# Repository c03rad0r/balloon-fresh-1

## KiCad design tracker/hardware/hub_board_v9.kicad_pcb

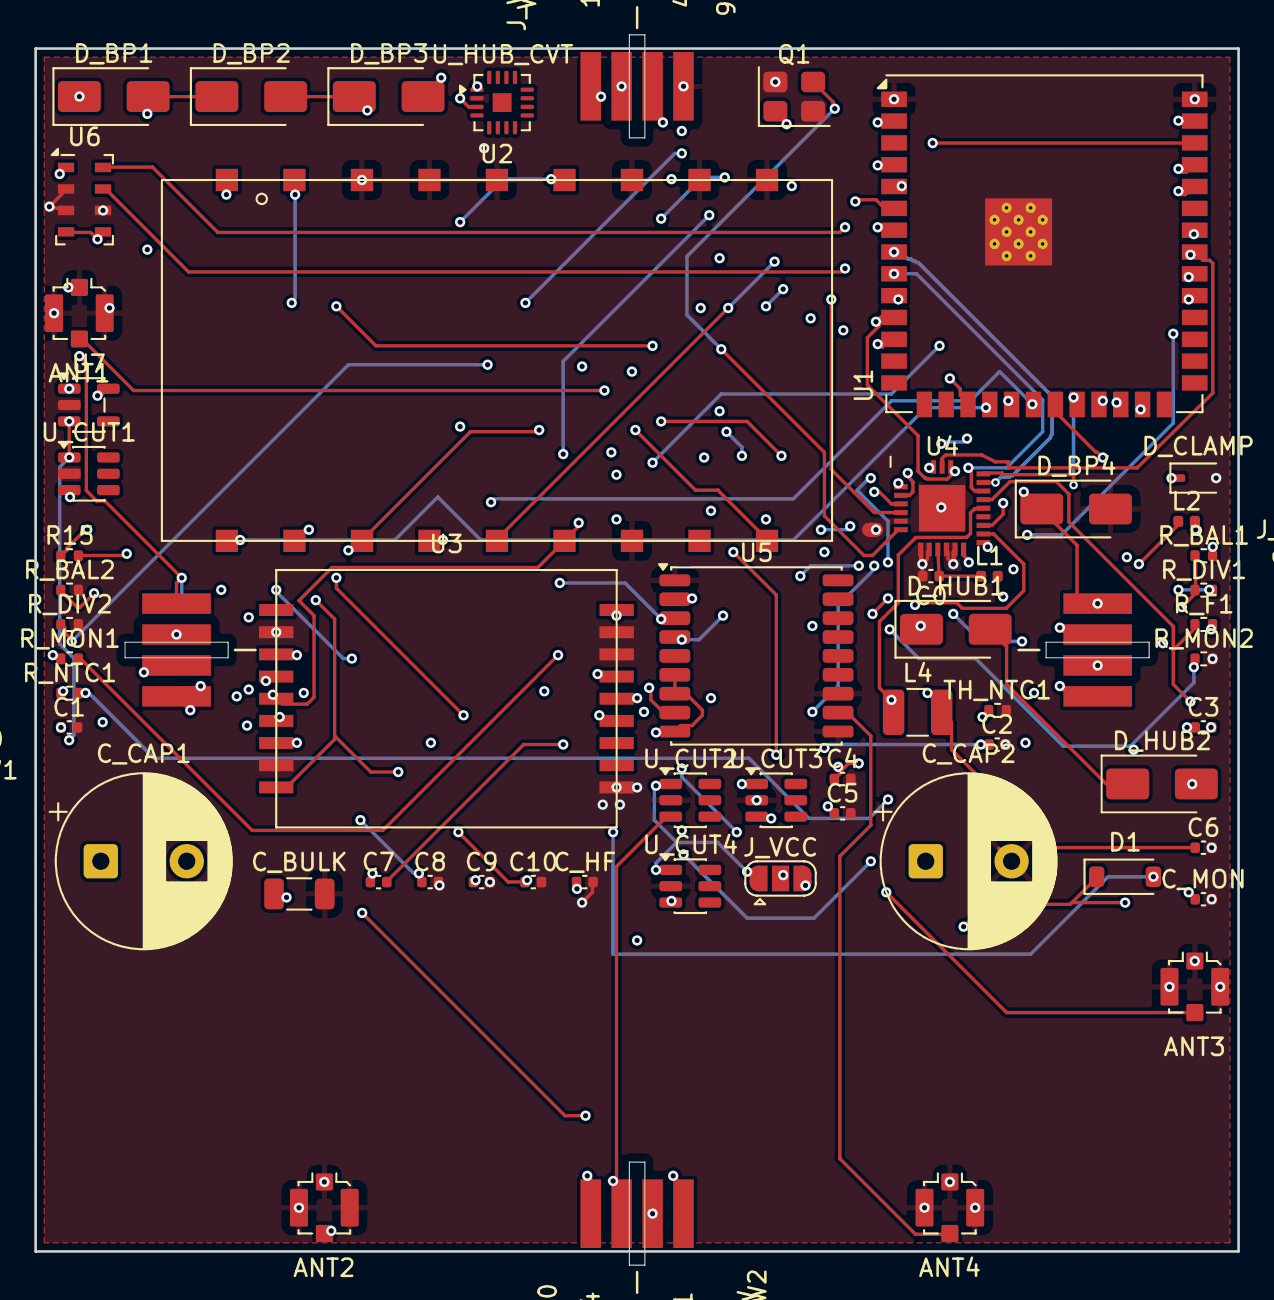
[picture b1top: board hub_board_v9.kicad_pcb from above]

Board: 4 copper layers, 70.0 x 71.6 mm, 59 parts (0 on the bottom side), 59 nets.

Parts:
ANT1: U.FL_433_TX; U.FL_Molex_MCRF_73412-0110_Vertical
ANT2: U.FL_2G4_RANGE; U.FL_Molex_MCRF_73412-0110_Vertical
ANT3: U.FL_2G4_RX; U.FL_Molex_MCRF_73412-0110_Vertical
ANT4: U.FL_GNSS_L1; U.FL_Molex_MCRF_73412-0110_Vertical
C0: 0.8pF; C_0402_1005Metric
C1, C2: 1.2pF; C_0402_1005Metric
C3: 100pF; C_0402_1005Metric
C4: 10uF; C_0402_1005Metric
C5, C6: 10nF; C_0402_1005Metric
C7: 0.5pF; C_0402_1005Metric
C8, C10: 100nF; C_0402_1005Metric
C9: 470nF; C_0402_1005Metric
C_BULK: 100uF; C_1206_3216Metric
C_CAP1, C_CAP2: 3.3F 2.7V (AVX SCC); CP_Radial_D10.0mm_P5.00mm
C_HF: 100nF; C_0402_1005Metric
C_MON: 10nF; C_0402_1005Metric
D1: BAT54; D_SOD-123
D_BP1, D_BP2, D_BP3, D_BP4: SS24; D_SMA
D_CLAMP: TVS clamp (set point TODO(unverified)); D_SOD-323
D_HUB1, D_HUB2: SS24; D_SMA
J_VCC: F33_VCC_SEL (5V raw | 3V3); SolderJumper-3_P1.3mm_Open_RoundedPad1.0x1.5mm
J_W1: WING_SOCKET_4P (hub wing interface 1); Wing_Tab_4P
J_W2: WING_SOCKET_4P (hub wing interface 2); Wing_Tab_4P
J_W3: WING_SOCKET_4P (hub wing interface 3); Wing_Tab_4P
J_W4: WING_SOCKET_4P (hub wing interface 4); Wing_Tab_4P
L1: 3.0nH; L_0402_1005Metric
L2: 2.5nH; L_0402_1005Metric
L4: 15uH; L_1210_3225Metric
Q1: 52MHz; Crystal_SMD_3225-4Pin_3.2x2.5mm
R15: 0R; R_0402_1005Metric
R_BAL1, R_BAL2: 10k; R_0402_1005Metric
R_DIV1, R_DIV2: 1M; R_0402_1005Metric
R_F1: 100R; R_0402_1005Metric
R_MON1, R_MON2: 4.7M; R_0402_1005Metric
R_NTC1: TODO(unverified) (sets ntc_r_ratio); R_0402_1005Metric
TH_NTC1: TODO(unverified) (NTC, R25/beta TODO); R_0402_1005Metric
U1: ESP32-S3-WROOM-1U-N8R8; ESP32-S3-WROOM-1U
U2: LoRa2021F33-2G4; LoRa2021F33_2G4
U3: LoRa2021_Castellated
U4: SX1280; SX1280_QFN24
U5: MAX-M10S; ublox_MAX
U6: MS5611-01BA; LGA-8_3x5mm_P1.25mm
U7: TPS7A02; SOT-23-5
U_CUT1, U_CUT2, U_CUT3, U_CUT4: SN74LVC1G373DBVR; SOT-23-6
U_HUB_CVT: BQ25504RGTR; VQFN-16-1EP_3x3mm_P0.5mm_EP1.1x1.1mm

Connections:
+3V3: C10.1, J_VCC.3, R15.1, R_F1.1, U1.2, U2.5, U3.1, U4.15, U5.6, U5.7, U5.9, U6.1, U6.4, U6.5, U7.5
/ANT1_433_TX: ANT1.1, U2.9
/ANT2_2G4_RANGE: ANT2.1, C3.2
/ANT3_2G4_RX: ANT3.1, U3.10
/ANT4_GNSS_L1: ANT4.1, U5.11
/CUT_SENSE_W1: J_W1.3, U_CUT1.3
/CUT_SENSE_W2: J_W2.3, U_CUT2.3
/CUT_SENSE_W3: J_W3.3, U_CUT3.3
/CUT_SENSE_W4: J_W4.3, U_CUT4.3
/F33_BUSY: U1.12, U2.14
/F33_CS_N: U1.7, U2.13
/F33_IRQ: U1.17, U2.18
/F33_MISO: U1.6, U2.16, U3.3
/F33_MOSI: U1.5, U2.15, U3.4
/F33_RESET_N: U1.18, U2.17
/F33_SCK: U1.4, U2.12, U3.5
/F33_VCC: C_BULK.1, C_HF.1, D_CLAMP.1, J_VCC.2, R_MON1.1, U2.1
/F33_VSENSE: C_MON.1, R_MON1.2, R_MON2.1, U1.21
/GNSS_PPS: U1.23, U5.4
/GNSS_RX: U1.37, U5.3
/GNSS_TX: U1.36, U5.2
/GNSS_VCC: C4.1, R_F1.2, U5.8
/HUB_PV_MID1: D_HUB1.2, D_HUB2.1
/HUB_PV_N: D_HUB2.2, U_HUB_CVT.3
/HUB_PV_P: D_HUB1.1, U_HUB_CVT.1
/I2C_SCL: U1.38, U6.8
/I2C_SDA: U1.39, U6.7
/NTC_SENSE: R_NTC1.2, TH_NTC1.1
/SCAP_ADC: R_DIV1.2, R_DIV2.1
/SCAP_MID: C_CAP1.2, C_CAP2.1, R_BAL1.2, R_BAL2.1
/SX1280_BUSY: U1.31, U4.7
/SX1280_CS_N: U1.10, U4.19
/SX1280_DCC_SW: L4.1, U4.14
/SX1280_DIO1: U1.33, U4.8
/SX1280_DIO2: U1.11, U4.9
/SX1280_DIO3: U1.34, U4.10
/SX1280_MISO: U1.9, U4.16
/SX1280_MOSI: U1.8, U4.17
/SX1280_RESET_N: U1.32, U4.3
/SX1280_RF: C0.1, L1.1, U4.22
/SX1280_RF_FILT: C2.1, C3.1, C7.2, L2.2
/SX1280_RF_MATCH: C1.1, C7.1, L1.2, L2.1
/SX1280_SCK: U1.22, U4.18
/SX1280_VBAT_IO: C8.1, R15.2, U4.11
/SX1280_VDD: C6.1, C9.1, L4.2, U4.2, U4.12
/SX1280_VR_PA: C5.1, U4.1
/SX1280_XTA: Q1.1, U4.4
/SX1280_XTB: Q1.3, U4.6
/U3_BUSY: U1.24, U3.7
/U3_CS_N: U1.20, U3.6
/U3_IRQ: U1.19, U3.15
/U3_RESET_N: U1.25, U3.14
/VSCAP: C_CAP1.1, D1.1, J_VCC.1, R_BAL1.1, R_DIV1.1, U7.1, U7.3, U_CUT1.1, U_CUT2.1, U_CUT3.1, U_CUT4.1
/VTCXO_VNTC: R_NTC1.1, U3.13
/W1_SOLAR_N: D_BP1.2, D_BP2.1, J_W1.4, J_W2.1
/W1_SOLAR_P: D1.2, D_BP1.1, J_W1.1
/W2_SOLAR_N: D_BP2.2, D_BP3.1, J_W2.4, J_W3.1
/W3_SOLAR_N: D_BP3.2, D_BP4.1, J_W3.4, J_W4.1
GND: ANT1.2, ANT2.2, ANT3.2, ANT4.2, C0.2, C1.2, C2.2, C4.2, C5.2, C6.2, C8.2, C9.2, C10.2, C_BULK.2, C_CAP2.2, C_HF.2, C_MON.2, D_BP4.2, D_CLAMP.2, J_W1.2, J_W2.2, J_W3.2, J_W4.2, J_W4.4, Q1.2, Q1.4, R_BAL2.2, R_DIV2.2, R_MON2.2, TH_NTC1.2, U1.1, U1.40, U1.41, U2.2, U2.3, U2.4, U2.6, U2.7, U2.8, U2.11, U3.2, U3.8, U3.11, U3.12, U3.18, U4.0, U4.5, U4.13, U4.20, U4.21, U4.23, U4.24, U5.1, U5.10, U5.12, U6.2, U6.3, U6.6, U7.2, U_CUT1.2, U_CUT2.2, U_CUT3.2, U_CUT4.2, U_HUB_CVT.2

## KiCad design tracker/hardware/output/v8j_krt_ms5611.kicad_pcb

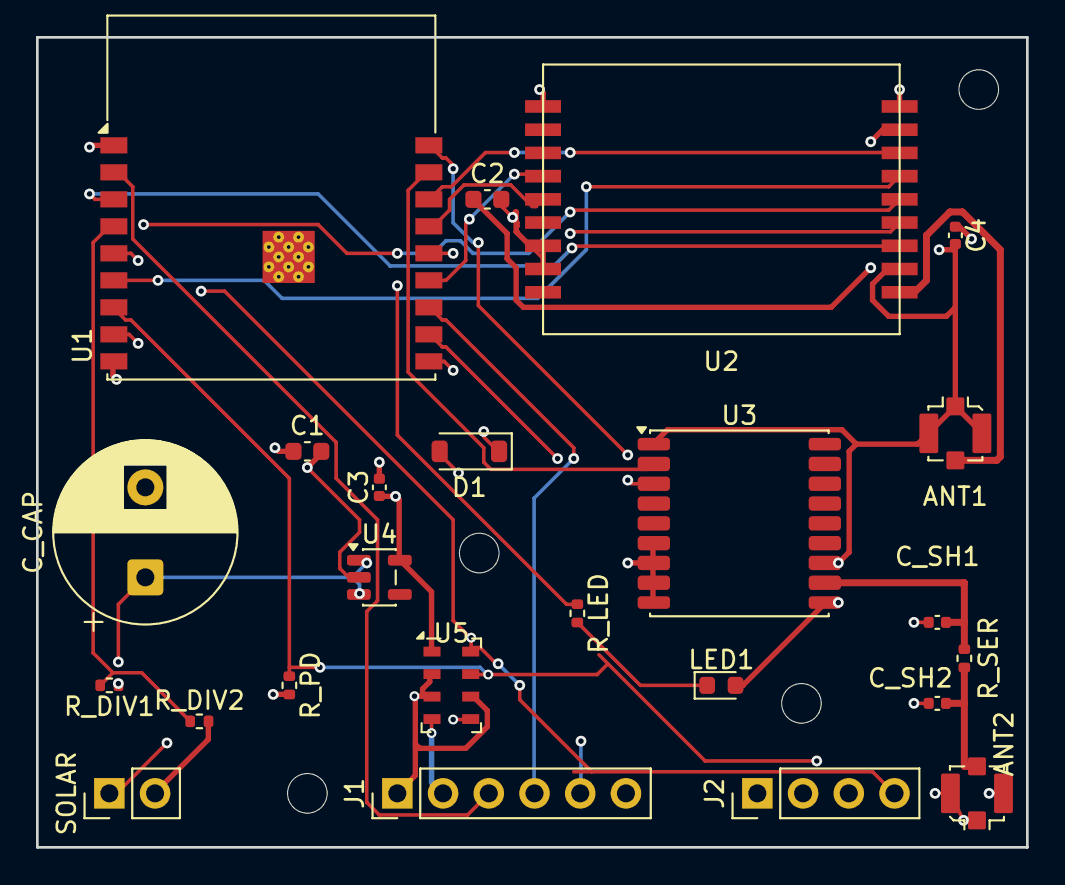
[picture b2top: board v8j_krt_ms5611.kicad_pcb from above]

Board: 4 copper layers, 55.0 x 45.0 mm, 28 parts (0 on the bottom side), 24 nets.

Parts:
ANT1: U.FL; U.FL_Molex_MCRF_73412-0110_Vertical
ANT2: U.FL_GNSS; U.FL_Molex_MCRF_73412-0110_Vertical
C1, C2: 10uF; C_0603_1608Metric
C3, C4: 100nF; C_0402_1005Metric
C_CAP: 1F_5.5V; CP_Radial_D10.0mm_P5.00mm
C_SH1, C_SH2: DNP; C_0402_1005Metric
D1: BAT54; D_SOD-123
J1: Prog_Header; PinHeader_1x06_P2.54mm_Vertical
J2: Debug_Header; PinHeader_1x04_P2.54mm_Vertical
LED1: LED_RED; LED_0603_1608Metric
MNT1, MNT2, MNT3, MNT4: MountingHole; MountingHole_2.2mm_M2
R_DIV1, R_DIV2: 100k; R_0402_1005Metric
R_LED: 330R; R_0402_1005Metric
R_PD: 10k; R_0402_1005Metric
R_SER: 0R; R_0402_1005Metric
SOLAR: Solar_In; PinHeader_1x02_P2.54mm_Vertical
U1: ESP32-C3-WROOM-02
U2: LoRa2021_Gen4; LoRa2021_Castellated
U3: MAX-M10S; ublox_MAX
U4: TPS7A02; SOT-23-5
U5: MS5611-01BA; LGA-8_3x5mm_P1.25mm

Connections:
+3V3: C1.1, C2.1, C3.1, C4.1, J1.2, J2.2, R_PD.2, U1.1, U2.1, U3.6, U3.7, U3.8, U3.9, U4.5, U5.1, U5.4, U5.5
EN: J1.3, U1.2
GND: ANT1.2, ANT2.2, C1.2, C2.2, C3.2, C4.2, C_CAP.2, C_SH1.1, C_SH2.1, J1.1, J2.1, LED1.2, R_DIV2.2, SOLAR.2, U1.9, U1.19, U2.2, U2.8, U2.11, U2.12, U2.18, U3.1, U3.10, U3.12, U4.2, U5.2, U5.3, U5.6
GNSS_ANT: ANT2.1, C_SH2.2, R_SER.1
GNSS_RF: C_SH1.2, R_SER.2, U3.11
GPS_RX: U1.17, U3.2
GPS_TX: U1.18, U3.3
I2C_SCL: J2.4, U1.8, U5.8
I2C_SDA: J2.3, R_PD.1, U1.7, U5.7
LED_A: LED1.1, R_LED.2
LED_DRIVE: R_LED.1, U1.14
LR_BUSY: U1.3, U2.7
LR_IRQ: U1.13, U2.15
LR_RST: U1.15, U2.14
RF_OUT: ANT1.1, U2.9
SOLAR_IN: D1.1, SOLAR.1
SPI_MISO: U1.16, U2.3
SPI_MOSI: U1.6, U2.4
SPI_NSS: U1.10, U2.6
SPI_SCK: U1.5, U2.5
UART0_RX: J1.5, U1.11
UART0_TX: J1.4, U1.12
VCAP: C_CAP.1, D1.2, R_DIV1.1, U4.1, U4.3
VDIV_MID: R_DIV1.2, R_DIV2.1, U1.4

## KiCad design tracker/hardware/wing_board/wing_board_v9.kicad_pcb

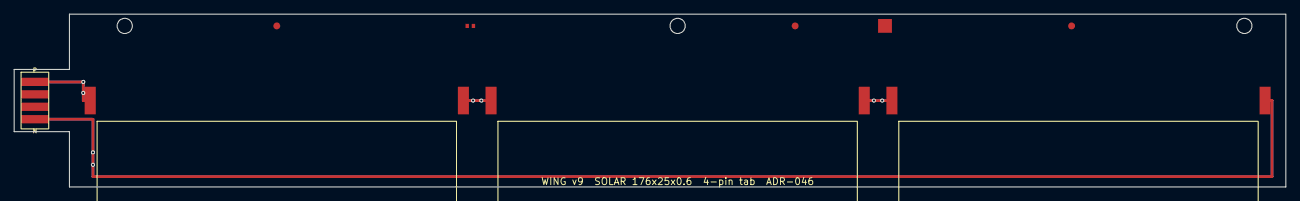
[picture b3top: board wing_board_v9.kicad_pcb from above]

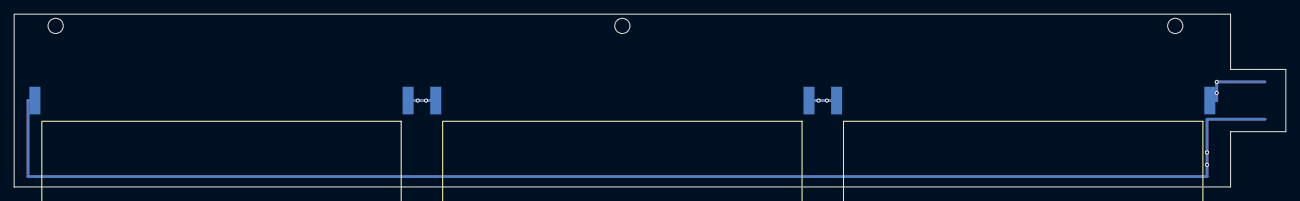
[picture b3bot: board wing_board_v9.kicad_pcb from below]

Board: 2 copper layers, 184.0 x 25.0 mm, 15 parts (3 on the bottom side), 4 nets.

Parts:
FB1: FerriteBead_0402_DNP_V2only; FerriteBead_0402_V2provision
FID1, FID2, FID3: Fiducial_1mm_Mask2mm
H1, H2, H3: MountingHole_NPTH_2.2mm; MountingHole_2.2mm_NPTH
J1: WingTab_v9_4pin
RF1: RF_ProvisionPad_v2only
SC1, SC2, SC3, SC4, SC5, SC6: SolarCell_52x19mm_0.5V; SolarCell_52x19mm

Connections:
SOLAR_MID1: SC1.2, SC2.1, SC4.2, SC5.1
SOLAR_MID2: SC2.2, SC3.1, SC5.2, SC6.1
SOLAR_N: J1.4, SC3.2, SC6.2
SOLAR_P: J1.1, SC1.1, SC4.1

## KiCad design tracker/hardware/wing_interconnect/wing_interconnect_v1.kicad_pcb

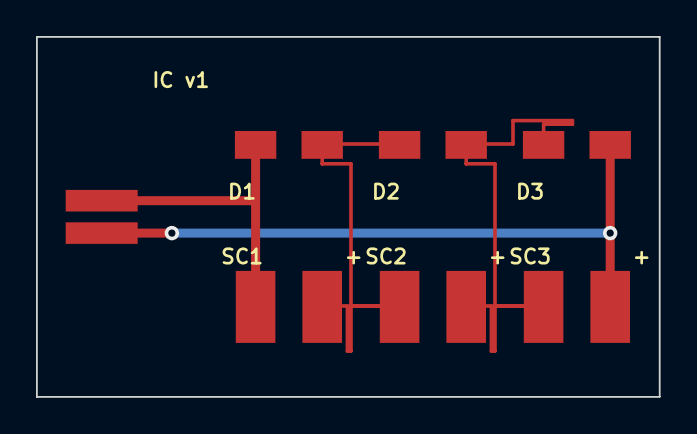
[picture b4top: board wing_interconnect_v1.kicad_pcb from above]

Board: 2 copper layers, 34.6 x 20.0 mm, 7 parts (0 on the bottom side), 4 nets.

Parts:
D1, D2, D3: D_SMA_Wing
J1: Tab_2P
SC1, SC2, SC3: SolarTail_2P

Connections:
SOLAR_MID1: D1.2, D2.1, SC1.2, SC2.1
SOLAR_MID2: D2.2, D3.1, SC2.2, SC3.1
SOLAR_N: D3.2, J1.2, SC3.2
SOLAR_P: D1.1, J1.1, SC1.1
